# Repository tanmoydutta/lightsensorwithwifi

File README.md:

<h1>ESP32-C3 based Light sensor</h1>

<h2>Description</h2>
This tiny module is designed around Espressief's ESP32-C3 System On a Chip. Purpose of this module is simple, measure the ambient or incident
light and communicate the reading through the chip's built-in WiFi interface. It uses AMS OSRAM TSL2591 sensor to measure the incident light.

Primary challenge has been to design an RF (Radio Frequency) optimised PCB (Printed Circuit Board) to accommodate this electronics. This designed is optimised for WiFi 2.4GHz and features a
chip antenna (Ignion's NN01-102) to minimize the board size (35mm x 20mm).

The PCB has been designed as per the hardware design guidelines from Espressief with one noticeable deviation on the thickness of the PCB (1.6mm instead of the recommended ~0.8mm)

RF part of the board has been tested with a VNA (Vector Network Analyser) and has been optimized with the help of a matching Pi-network. 
Antenna traces are also designed based upon the datasheet specification and recommended trace pattern.

This hardware has been certified with Open Source Hardware Association

<h2>The Module</h2>
End result of the PCB is a 4 layer design and manufactured with the help of JLC PCB (https://jlcpcb.com) which according to their documentation has a 
dielectric constant of 4.5 for FR-4 type material. 

The light sensor is mounted on the back side of the board as depicted below -

Here is a size reference for the end module - 

<h2>Enclosure</h2>
I went ahead and also designed a 3D model for the housing of this module for application - 

<h2>Programming</h2>
Add your own firmware and code to make use of the built-in sensor and indicator. This module can be programmed using Arduino or ESP-IDF IDE. This module has a 
close resemblance with LOLIN C3 Mini or Adafruit C3 QTPy, hence those core board definitions are compatible with this module.

<h2>Design and Architecture</h2>
Below is the System Context for this module highlighting 
the interfaces and interactions with this module. 

Also a blown up building block of functionality within.

<h2>Applications</h2>
One implementation that I personally use this module is for the purpose of controlling the lights on my balcony and eventually also festive lights during Christmas.
Following a possible application diagram -

<h2>Open Source Hardware</h2>
This board is an OSHWA approved design: <a href="https://certification.oshwa.org/nl000015.html">NL000015</a>

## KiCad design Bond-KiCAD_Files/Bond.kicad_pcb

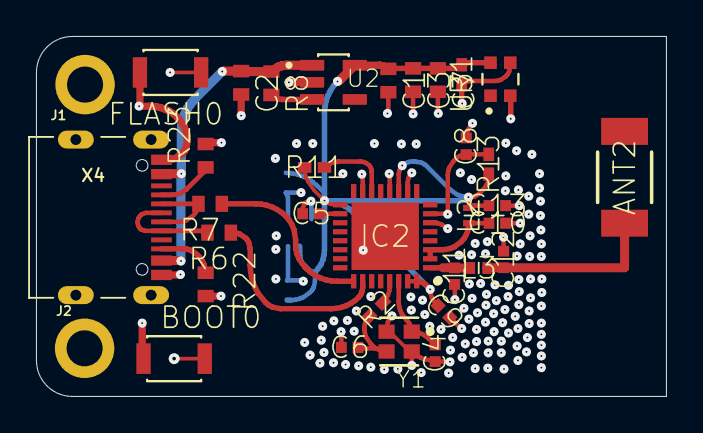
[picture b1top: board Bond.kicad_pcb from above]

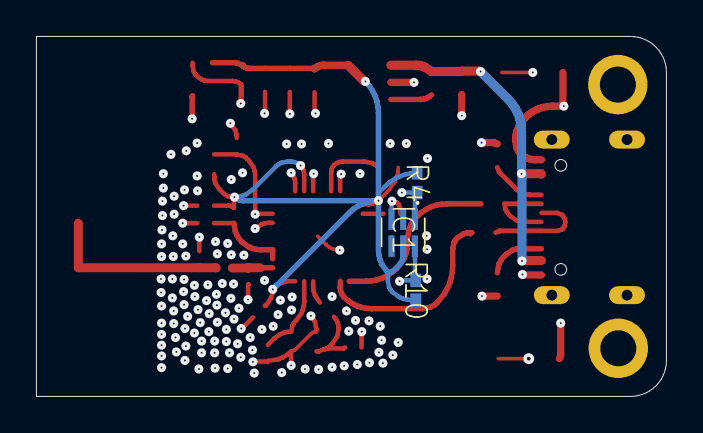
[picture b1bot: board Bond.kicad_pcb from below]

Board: 4 copper layers, 35.0 x 20.0 mm, 37 parts (3 on the bottom side), 23 nets.

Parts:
ANT2: NN01-102; NN01102
BOOT0: B3U-1000P; SW_B3U-1000P
C1: 1uF; C0402
C2, C3: 10uF; C0402
C4, C6: 8pF; CAPC1005X55N
C5, C8: 1uF; CAPC1005X55N
C7: 100nF; C0402
C9, C10, C13: 100nF; CAPC1005X55N
C11, C12: NC; CAPC1005X55N
FLASH0: B3U-1000P; SW_B3U-1000P
IC1: TSL25913FN
IC2: ESP32-C3FH4; QFN50P500X500X90-33N
J1, J2: 1X01_2MM
L2: 2nH; LQG15WH0N7B02D
L3: 1.2nH; LQW15CNR20J00B
R1, R11, R13: 10K; RESC1005X40N
R2: 0R; RESC1005X40N
R4, R10: 4.7K; RESC1005X40N
R6, R7: 22R; R0402
R8: 100K; R0402
R22, R23: 5.1K; R0402
U2: AP2112K-3.3TRG1; SOT95P285X140-5N
U3: WS2812-2020; LED_WS2812-2020
X4: MICROBUILDER_USB_C_CUSB31-CFM2AX-01-X
Y1: 40MHz; KYOCERA_INTERNATIONAL_INC._ELECTRONIC_COMPONENTS_CX2016DB40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

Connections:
ANT: C11.1, IC2.1, L3.1
D+: IC2.26, R6.1
D-: IC2.25, R7.1
EN: BOOT0.2, C8.1, IC2.7, R13.2
GND: BOOT0.1, C1.2, C2.2, C3.2, C4.2, C5.2, C6.2, C7.2, C8.2, C9.2, C10.2, C11.2, C12.2, C13.2, FLASH0.1, IC1.3, IC2.33, J1.1, J2.1, R22.2, R23.2, U2.2, U3.2, X4.A1B12, X4.B1A12, Y1.2, Y1.4
GPIO8: IC2.14, R11.2
GPIO9: FLASH0.2, IC2.15
unnamed: C5.1, IC2.18
unnamed: ANT2.1, C12.1, L3.2
unnamed: C10.1, IC2.2, IC2.3, L2.2
unnamed: IC2.29, R2.2
unnamed: R22.1, X4.B5
unnamed: R23.1, X4.A5
unnamed: R7.2, X4.A7, X4.B7
unnamed: R6.2, X4.A6, X4.B6
unnamed: R8.2, U2.3
NEOPIX: IC2.6, R1.2, U3.3
SCL: IC1.1, IC2.12, R4.2
SDA: IC1.6, IC2.10, R10.2
VBUS: C2.1, R8.1, U2.1, X4.A4B9, X4.B4A9
VCCIO: C1.1, C3.1, C7.1, C9.1, C13.1, IC1.5, IC2.11, IC2.17, IC2.31, IC2.32, L2.1, R1.1, R4.1, R10.1, R11.1, R13.1, U2.5, U3.4
XN: C6.1, R2.1, Y1.3
XP: C4.1, IC2.30, Y1.1

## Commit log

2023-09-21 Adding Bond files
2023-09-21 Adding Bond in enclosure image
2023-09-21 Update README.md
    First documentation with images
2023-09-21 Image size adjusted
2023-09-21 Update README.md
    Added further details
2023-09-21 System Architecture and aplication diagrams
2023-09-21 Update README.md
    Updated additional info and created sections
2023-09-21 Updated the Building block diagram
2023-09-21 Adding Sensor slot image
2023-09-21 Update README.md
    Added image
2023-09-26 Adding correct 3D file for the PCB
2023-09-27 Update README.md
    Added OSHWA certification link
2023-09-27 Adding a sample source code to operate the unit
2023-09-27 Adding OSHWA certificate mark
2023-09-27 Update README.md
    Adding OSHWA Certificate
2023-09-27 Update README.md
    Adjusting broken link
